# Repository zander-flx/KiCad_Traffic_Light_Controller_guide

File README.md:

# KiCad_Traffic_Light_Controller_guide

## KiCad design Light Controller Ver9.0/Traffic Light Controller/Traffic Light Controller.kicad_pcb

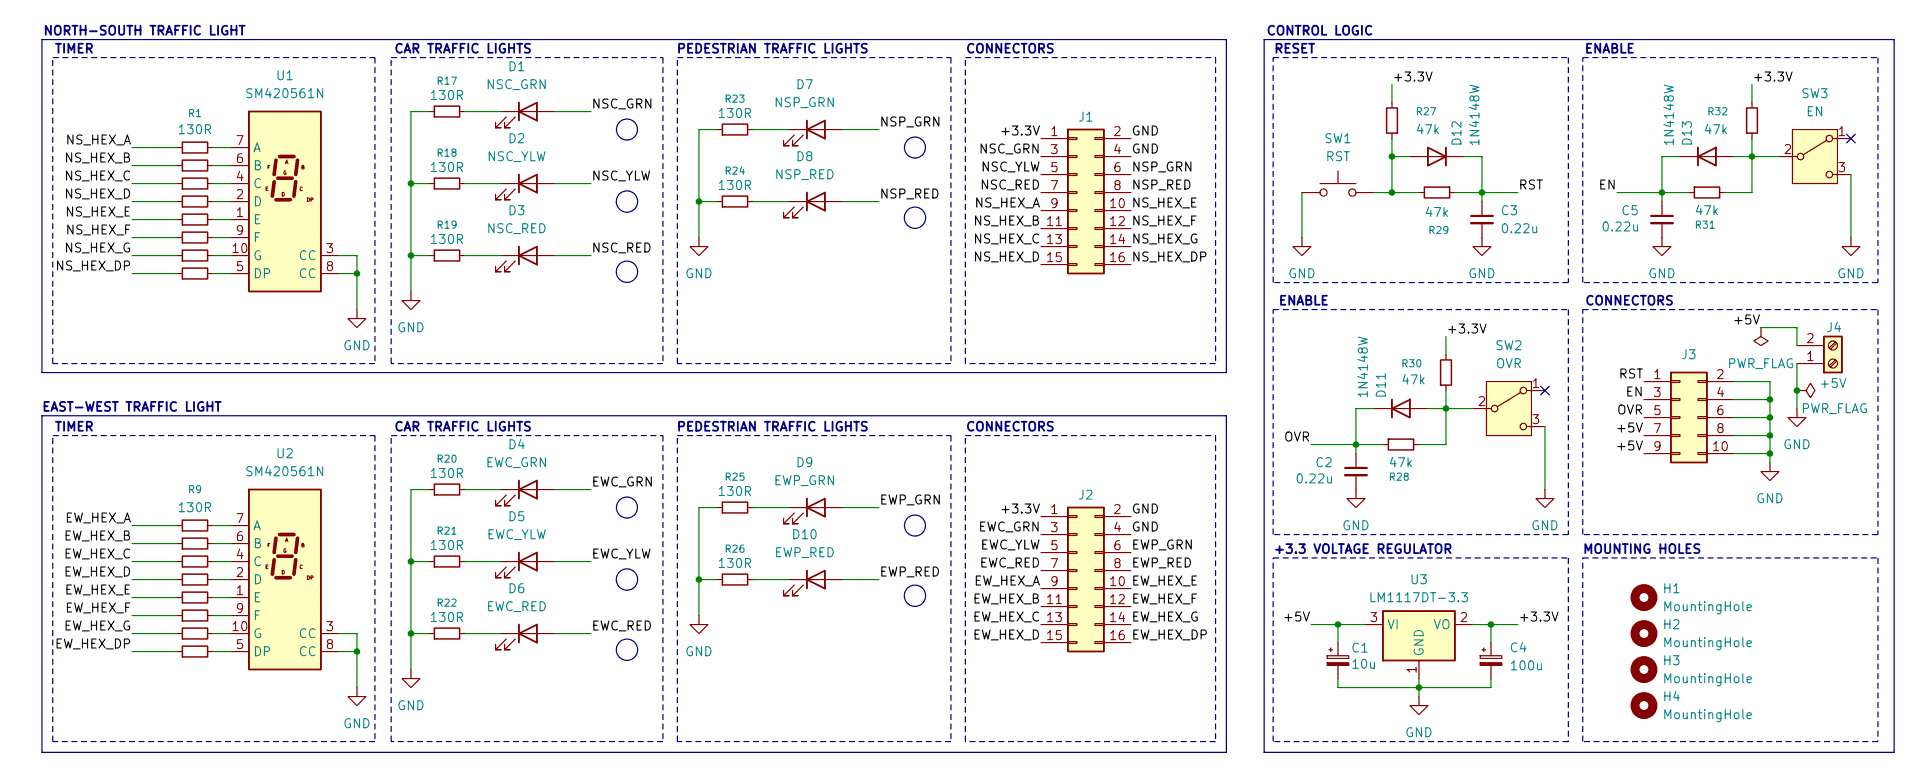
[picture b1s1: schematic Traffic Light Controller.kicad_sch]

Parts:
C1: 10u; CP_Elec_4x5.3
C2, C3, C5: 0.22u; C_1206_3216Metric_Pad1.33x1.80mm_HandSolder
C4: 100u; CP_Elec_6.3x5.8
D1: NSC_GRN; LED_D5.0mm
D2: NSC_YLW; LED_D5.0mm
D3: NSC_RED; LED_D5.0mm
D4: EWC_GRN; LED_D5.0mm
D5: EWC_YLW; LED_D5.0mm
D6: EWC_RED; LED_D5.0mm
D7: NSP_GRN; LED_D5.0mm
D8: NSP_RED; LED_D5.0mm
D9: EWP_GRN; LED_D5.0mm
D10: EWP_RED; LED_D5.0mm
D11, D12, D13: 1N4148W; D_SOD-123
H1, H2, H3, H4: MountingHole; MountingHole_2.2mm_M2
J1, J2: Conn_02x08_Odd_Even; PinHeader_2x08_P2.54mm_Vertical
J3: Conn_02x05_Odd_Even; PinHeader_2x05_P2.54mm_Vertical
J4: +5V; Terminal_Block_5mm
R1, R2, R3, R4, R5, R6, R7, R8, R9, R10, R11, R12, R13, R14, R15, R16, R17, R18, R19, R20, R21, R22, R23, R24, R25, R26: 130R; R_1206_3216Metric_Pad1.30x1.75mm_HandSolder
R27, R28, R29, R30, R31, R32: 47k; R_1206_3216Metric_Pad1.30x1.75mm_HandSolder
SW1: RST; tact_switch_5mm
SW2: OVR; slide_switch_2.54mm
SW3: EN; slide_switch_2.54mm
U1, U2: SM420561N; 7SegmentLED_LTS6760_LTS6780
U3: LM1117DT-3.3; SOT-223

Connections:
/+3.3V: C4.1, J1.1, J2.1, R27.2, R30.2, R32.2, U3.2 (VO)
/+5V: C1.1, J3.7, J3.9, J4.2, U3.3 (VI)
/EN: C5.1, D13.1 (K), J3.3, R31.1
/EWC_GRN: D4.2 (A), J2.3
/EWC_RED: D6.2 (A), J2.7
/EWC_YLW: D5.2 (A), J2.5
/EWP_GRN: D9.2 (A), J2.6
/EWP_RED: D10.2 (A), J2.8
/EW_HEX_A: J2.9, R9.1
/EW_HEX_B: J2.11, R10.1
/EW_HEX_C: J2.13, R11.1
/EW_HEX_D: J2.15, R12.1
/EW_HEX_DP: J2.16, R16.1
/EW_HEX_E: J2.10, R13.1
/EW_HEX_F: J2.12, R14.1
/EW_HEX_G: J2.14, R15.1
/NSC_GRN: D1.2 (A), J1.3
/NSC_RED: D3.2 (A), J1.7
/NSC_YLW: D2.2 (A), J1.5
/NSP_GRN: D7.2 (A), J1.6
/NSP_RED: D8.2 (A), J1.8
/NS_HEX_A: J1.9, R1.1
/NS_HEX_B: J1.11, R2.1
/NS_HEX_C: J1.13, R3.1
/NS_HEX_D: J1.15, R4.1
/NS_HEX_DP: J1.16, R8.1
/NS_HEX_E: J1.10, R5.1
/NS_HEX_F: J1.12, R6.1
/NS_HEX_G: J1.14, R7.1
/OVR: C2.1, D11.1 (K), J3.5, R28.1
/RST: C3.1, D12.1 (K), J3.1, R29.1
GND: C1.2, C2.2, C3.2, C4.2, C5.2, J1.2, J1.4, J2.2, J2.4, J3.2, J3.4, J3.6, J3.8, J3.10, J4.1, R17.1, R18.1, R19.1, R20.1, R21.1, R22.1, R23.1, R24.1, R25.1, R26.1, SW1.1, SW2.3 (C), SW3.3 (C), U1.3 (CC), U1.8 (CC), U2.3 (CC), U2.8 (CC), U3.1 (GND)
unnamed: D1.1 (K), R17.2
unnamed: D2.1 (K), R18.2
unnamed: D3.1 (K), R19.2
unnamed: D4.1 (K), R20.2
unnamed: D5.1 (K), R21.2
unnamed: D6.1 (K), R22.2
unnamed: D7.1 (K), R23.2
unnamed: D8.1 (K), R24.2
unnamed: D9.1 (K), R25.2
unnamed: D10.1 (K), R26.2
unnamed: D11.2 (A), R28.2, R30.1, SW2.2 (B)
unnamed: D12.2 (A), R27.1, R29.2, SW1.2
unnamed: D13.2 (A), R31.2, R32.1, SW3.2 (B)
unnamed: R1.2, U1.7 (A)
unnamed: R2.2, U1.6 (B)
unnamed: R3.2, U1.4 (C)
unnamed: R4.2, U1.2 (D)
unnamed: R8.2, U1.5 (DP)
unnamed: R5.2, U1.1 (E)
unnamed: R6.2, U1.9 (F)
unnamed: R7.2, U1.10 (G)
unnamed: R9.2, U2.7 (A)
unnamed: R10.2, U2.6 (B)
unnamed: R11.2, U2.4 (C)
unnamed: R12.2, U2.2 (D)
unnamed: R16.2, U2.5 (DP)
unnamed: R13.2, U2.1 (E)
unnamed: R14.2, U2.9 (F)
unnamed: R15.2, U2.10 (G)

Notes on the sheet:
EAST-WEST TRAFFIC LIGHT
CAR TRAFFIC LIGHTS
CONTROL LOGIC
ENABLE
TIMER
MOUNTING HOLES
CONNECTORS
+3.3 VOLTAGE REGULATOR
PEDESTRIAN TRAFFIC LIGHTS
RESET
NORTH-SOUTH TRAFFIC LIGHT

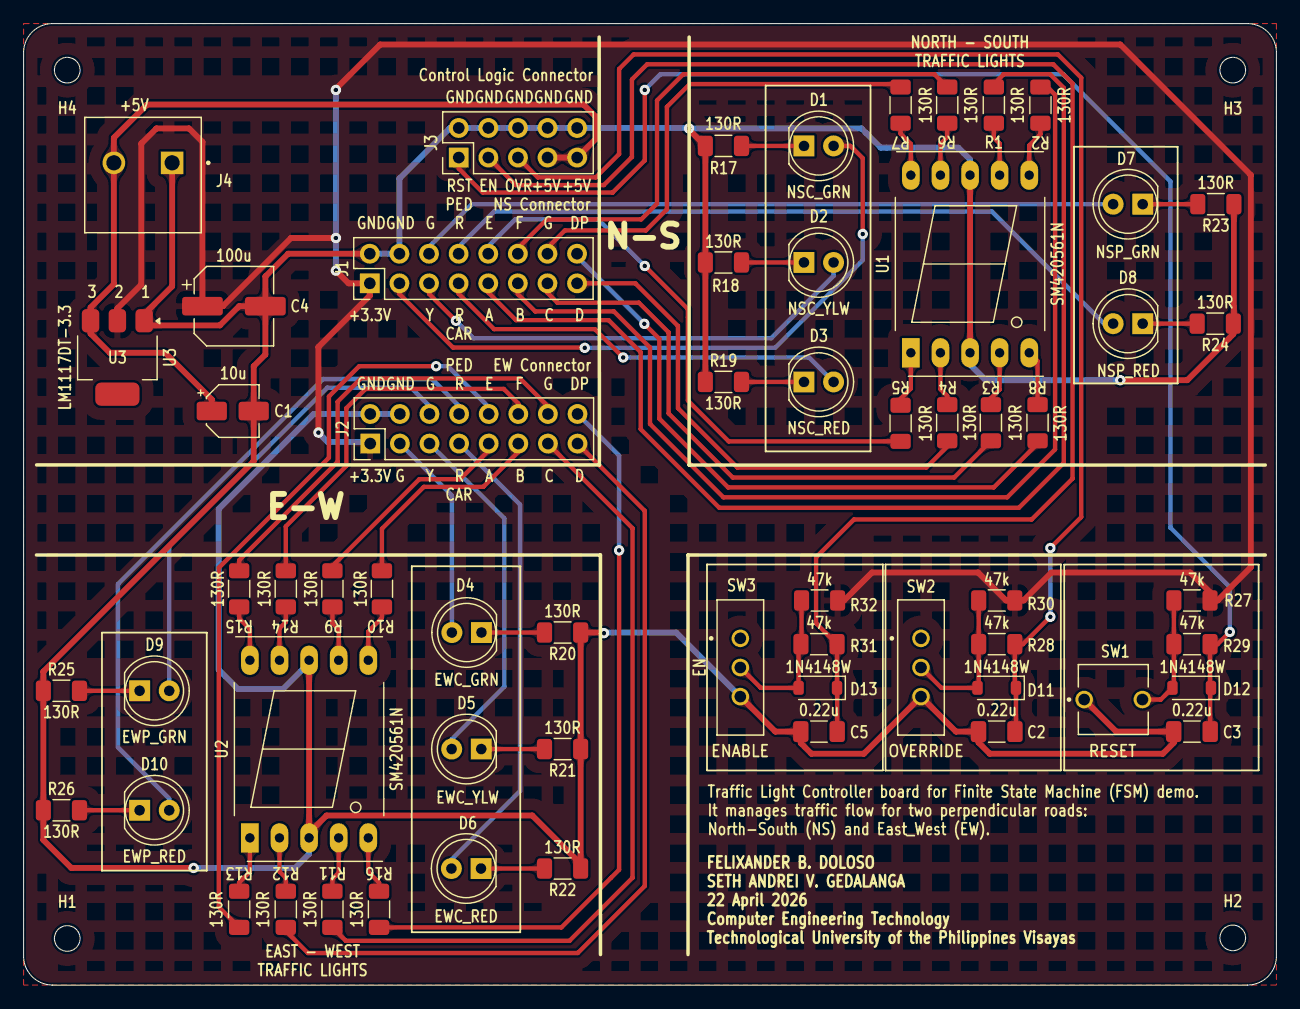
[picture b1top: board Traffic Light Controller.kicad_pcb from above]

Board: 2 copper layers, 107.5 x 82.5 mm, 64 parts (0 on the bottom side), 61 nets.

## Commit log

2026-04-18 Updated 04/18/26 (22:20)
2026-04-18 Updated 04/18/26 (22:21)
2026-04-20 Updated 04/20/26 (11:14)
2026-04-20 Updated 04/20/26 (11:26)
2026-04-21 Updated 04/21/26 (20:16)
2026-04-22 Updated 04/22/26 (21:33)
2026-04-23 Updated 4/23/26 (13:08)
2026-04-23 Updated 04/23/26 (13:10)
2026-05-04 Updated 05/04/26 (14:30)
2026-05-04 Updated 05/04/26 (16:06)
